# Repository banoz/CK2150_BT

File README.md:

# CK2150_BT
Adding Bluetooth and Wireless charging to CK2150 scales

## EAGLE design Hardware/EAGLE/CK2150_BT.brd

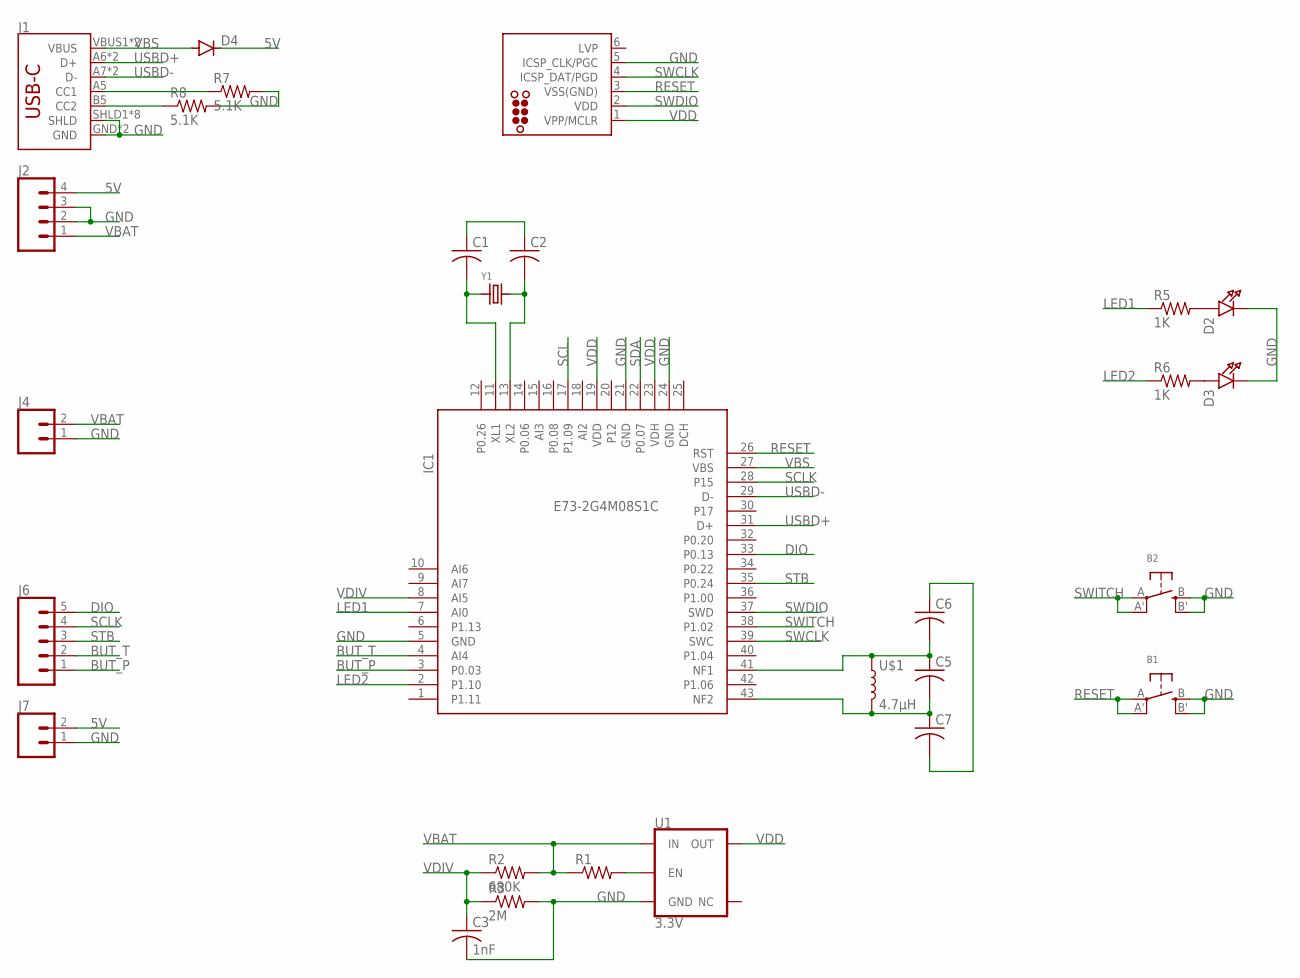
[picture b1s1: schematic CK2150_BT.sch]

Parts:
B1, B2: SWITCH_TACT_SMT4.6X2.8; BTN_KMR2_4.6X2.8
C1, C2, C5, C6, C7: C-USC0603; C0603
C3: 1nF; C0603
D2, D3: LED0805_NOOUTLINE; CHIPLED_0805_NOOUTLINE
D4: DIODE-SOD123; SOD123; LCSC C511872
IC1: E73-2G4M08S1C; SMD
J1: USB_C5; USB-C-16P-5
J2: CONN_041X04_NO_SILK; 1X04_NO_SILK
J3: TC2030-MCP-NL
J4, J7: CONN_021X02_NO_SILK; 1X02_NO_SILK
J6: CONN_05NO_SILK; 1X05_NO_SILK
R1: R-US_R0603; R0603
R2: 680K; R0603
R3: 2M; R0603
R5, R6: 1K; R0603
R7, R8: 5.1K; R0603
U1: 3.3V; SOT23-5
U$1: 4.7μH; W3102
Y1: CRYSTAL8X3.8SMT; CRYSTAL_8X3.8

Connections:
5V: D4.C, J2.4, J7.2
BUT_P: IC1.3 (P0.03), J6.1
BUT_T: IC1.4 (AI4), J6.2
DIO: IC1.33 (P0.13), J6.5
GND: B1.B (S), B1.B' (S1), B2.B (S), B2.B' (S1), C1.1, C2.1, C3.2, C6.1, C7.2, D2.C, D3.C, IC1.5 (GND), IC1.21 (GND), IC1.24 (GND), J1.GND, J1.GND2 (GND), J1.SHLD1 (SHLD), J1.SHLD2 (SHLD), J1.SHLD3 (SHLD), J1.SHLD4 (SHLD), J1.SHLD5 (SHLD), J1.SHLD6 (SHLD), J1.SHLD7 (SHLD), J1.SHLD8 (SHLD), J2.2, J2.3, J3.5 (ICSP_CLK/PGC), J4.1, J7.1, R3.2, R7.2, R8.2, U1.2 (GND)
LED1: IC1.7 (AI0), R5.1
LED2: IC1.2 (P1.10), R6.1
unnamed: R1.2, U1.3 (EN)
unnamed: J1.A5 (CC1), R7.1
unnamed: C2.2, IC1.13 (XL2), Y1.P$4 (2)
unnamed: D2.A, R5.2
unnamed: C5.1, C6.2, IC1.41 (NF1), U$1.1
unnamed: C5.2, C7.1, IC1.43 (NF2), U$1.2
unnamed: D3.A, R6.2
unnamed: J1.B5 (CC2), R8.1
unnamed: C1.2, IC1.11 (XL1), Y1.P$1 (1)
RESET: B1.A, B1.A' (P1), IC1.26 (RST), J3.3 (VSS(GND))
SCL: IC1.17 (P1.09)
SCLK: IC1.28 (P15), J6.4
SDA: IC1.22 (P0.07)
STB: IC1.35 (P0.24), J6.3
SWCLK: IC1.39 (SWC), J3.4 (ICSP_DAT/PGD)
SWDIO: IC1.37 (SWD), J3.2 (VDD)
SWITCH: B2.A, B2.A' (P1), IC1.38 (P1.02)
USBD+: IC1.31 (D+), J1.A6 (D+), J1.B6 (D+)
USBD-: IC1.29 (D-), J1.A7 (D-), J1.B7 (D-)
VBAT: J2.1, J4.2, R1.1, R2.2, U1.1 (IN)
VBS: D4.A, IC1.27 (VBS), J1.VBUS1 (VBUS), J1.VBUS2 (VBUS)
VDD: IC1.19 (VDD), IC1.23 (VDH), J3.1 (VPP/MCLR), U1.5 (OUT)
VDIV: C3.1, IC1.8 (AI5), R2.1, R3.1

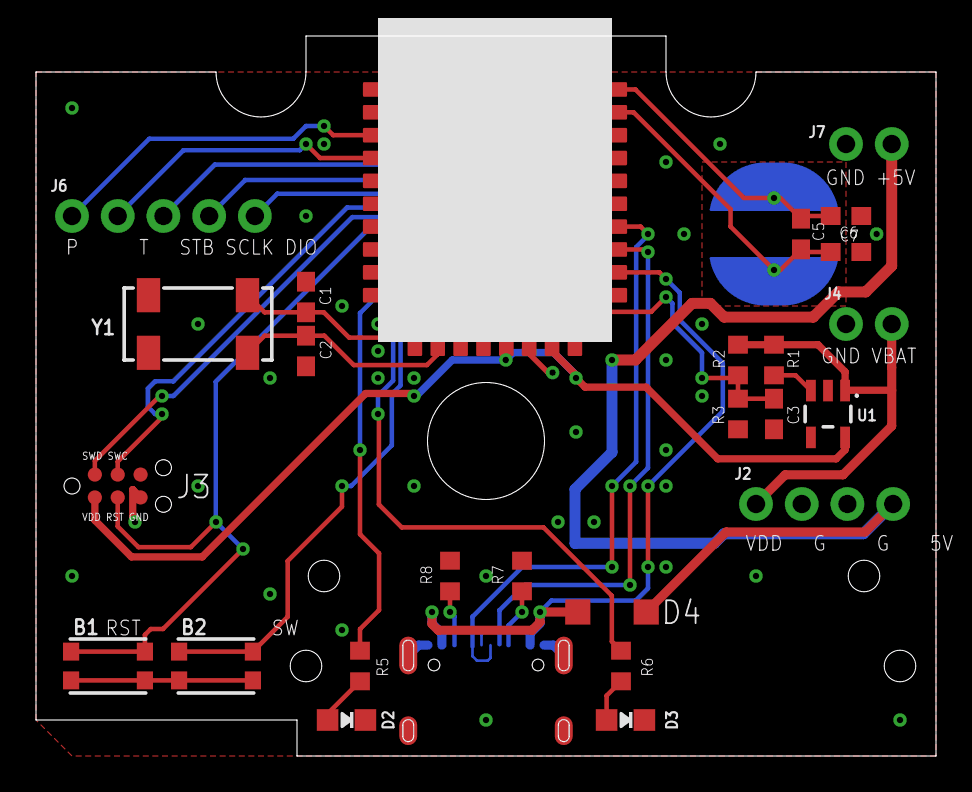
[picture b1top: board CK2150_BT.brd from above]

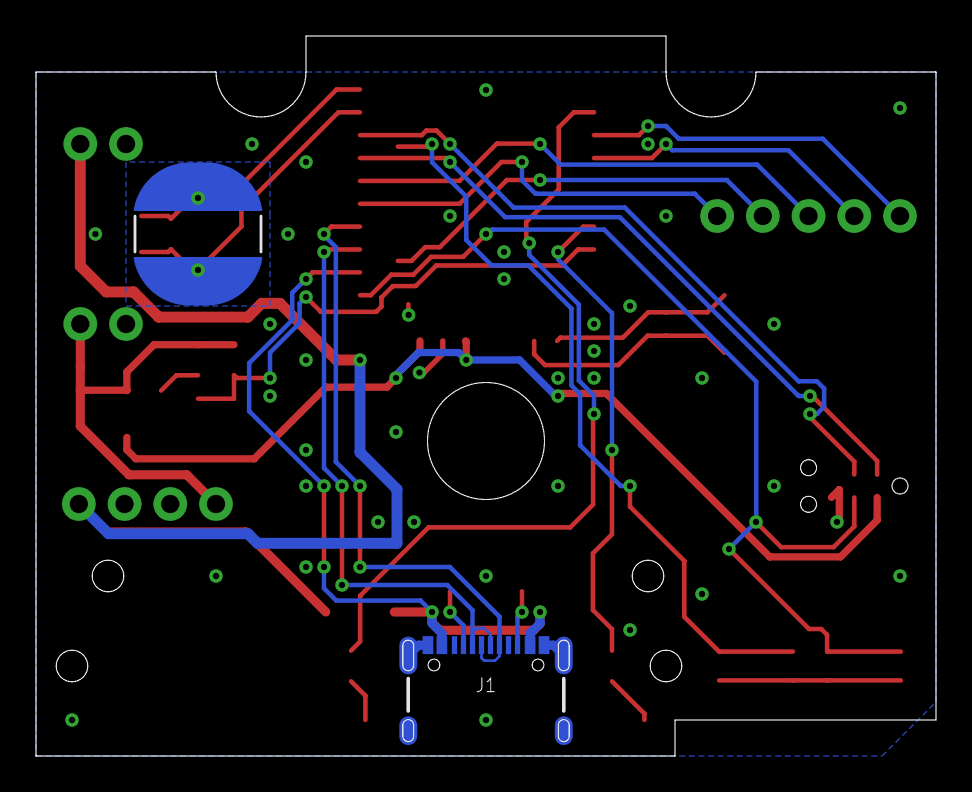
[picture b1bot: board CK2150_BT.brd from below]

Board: 2 copper layers, 50.0 x 40.0 mm, 28 parts (2 on the bottom side), 28 nets.

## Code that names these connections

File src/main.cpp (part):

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#define DEBUG_PRINTLNF(x, y)
#endif

#define DIO 25   // P0.13
#define SCLK 24  // P0.15
#define STB 1    // P0.24
#define BUT_P 19 // P0.03
#define BUT_T 17 // P0.28
#define LED_L 18 // P0.02
#define LED_R 4  // P1.10

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int16_t previousWeight, currentWeight;
int16_t previousTime, currentTime;

#define SPIS_CS_PIN ((uint32_t)24)   // STB
#define SPIS_MOSI_PIN ((uint32_t)13) // DIO
#define SPIS_SCK_PIN ((uint32_t)15)  // SCLK

#define SPIS_INSTANCE 0                                            /**< SPIS instance index. */
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  DEBUG_PRINTLN("Starting...");
#endif

  pinMode(BUT_P, INPUT);
  pinMode(BUT_T, INPUT);
  pinMode(LED_L, OUTPUT_D0H1);
  pinMode(LED_R, OUTPUT_D0H1);
  pinMode(PIN_VBAT, INPUT);
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  {
    if (inTareUpdateMillis == 0UL)
    {
      pinMode(BUT_T, OUTPUT_S0D1);
      digitalWrite(BUT_T, LOW);
      inTareUpdateMillis = millis() + 100UL;
    }
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    {
      isInTare = false;
      digitalWrite(BUT_T, HIGH);
      pinMode(BUT_T, INPUT);
      tareCounter++;
      notifyTareDone();
    }
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
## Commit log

2023-04-02 name fix
2025-02-25 deep sleep
2025-02-26 reduce timeout
2025-02-27 payload reduce to the limit

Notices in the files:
parts and their libraries:
SparkFun-Connectors: Licensing: Creative Commons ShareAlike 4.0 International - https://creativecommons.org/licenses/by-sa/4.0
microbuilder: This work is placed in the public domain, and may be freely used for commercial and non-commercial work with the following conditions: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
